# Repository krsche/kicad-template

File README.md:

# kicad-template

This repository can be used as a template for a new KiCad project.

__Features:__  
- `kicad-library` submodule included and set up for sharing custom footprints, symbols, etc.
- GitHub workflows using kibot for outputs (gerbers, pdfs, renders, etc.) and performing checks (erc, drc)
- `bootstrap.sh` script for quickly renaming your project (no need for importing this as an "OEM - KiCad Template")
- `.gitattributes` and `.gitignore` for KiCad
- Custom Design Rules according to [JLCPCB Capabilities](https://jlcpcb.com/capabilities/pcb-capabilities); modified version of https://github.com/labtroll/KiCad-DesignRules

## Getting Started
1. Create and clone a new GitHub repo for your project and select this as the template for it.
     ```bash
     gh repo create --clone --template krsche/kicad-template YOUR_REPO_NAME
     cd YOUR_REPO_NAME
     git submodule update --init --recursive
     ```
2. Run the `bootstrap.sh` script to change the name of the project files and references to your projects name. 
     Either specify the name by providing it as the first argument, or specify nothing and it will use the parent folder (repo) name.
     ```bash
     ./bootstrap.sh <OPTIONAL__PROJECT_NAME>
     ```
3. Change the `README.md`
4. Update the `LICENSE`
5. Commit the changes after running the `bootstrap.sh` script
     ```bash
     git add --all
     git commit -m "feat: bootstrap"
     git push
     ```

## Releasing
1. Observe the GH Actions already run on the commit you want to release.
     Everything looks good? --> Continue
2. Tag the commit in the format `v1.0.0` and push the tag
3. Observe the new GH Action that runs. 
     It will re-run the KiBot actions and create __a new GH Release__ with the outputs from KiBot.

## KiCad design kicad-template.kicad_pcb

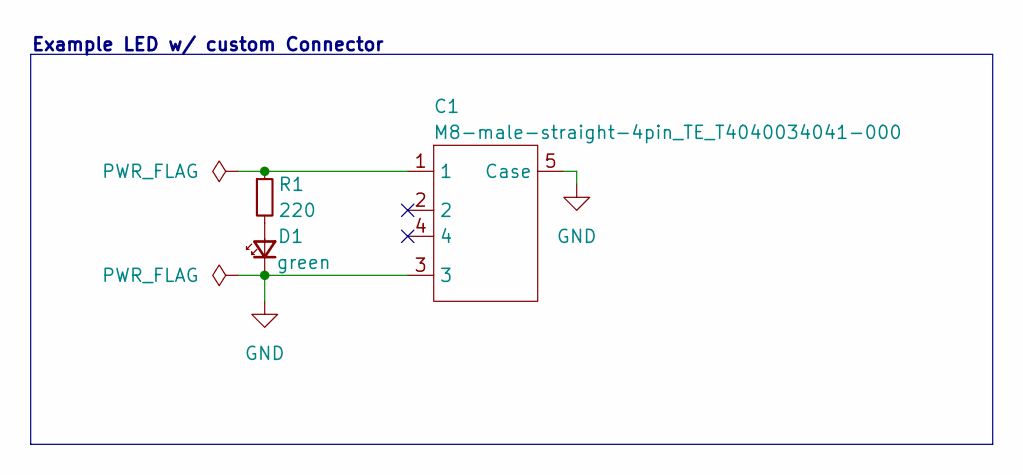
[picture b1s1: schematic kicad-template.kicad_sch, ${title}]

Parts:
C1: M8-male-straight-4pin_TE_T4040034041-000; Conn_M8_male_straight_4pin_TE_T4040034041-000; Part-Nr-Digikey A126810-ND
D1: green; LED_0603_1608Metric_Pad1.05x0.95mm_HandSolder
R1: 220; R_0603_1608Metric_Pad0.98x0.95mm_HandSolder

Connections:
GND: C1.3, C1.5 (Case), D1.1 (K)
unnamed: C1.1, R1.1
unnamed: D1.2 (A), R1.2

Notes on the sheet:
Example LED w/ custom Connector

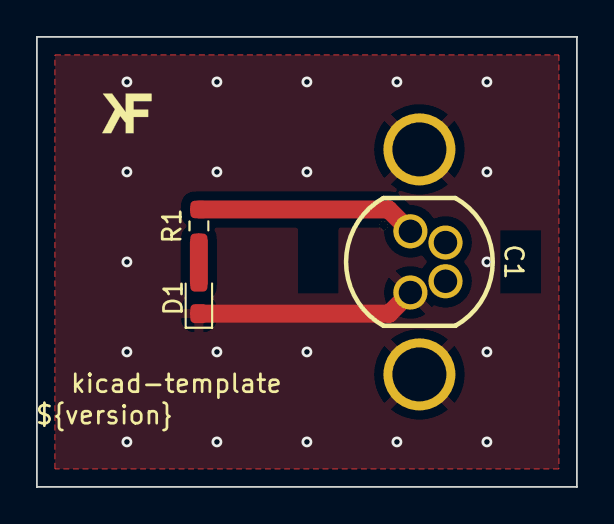
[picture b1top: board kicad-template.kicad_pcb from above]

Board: 4 copper layers, 30.0 x 25.0 mm, 3 parts (0 on the bottom side), 3 nets.

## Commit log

2022-04-21 Initial Commit
    based on trackdocs/can-socketstrip 79080c2d84e71ce2d29c4d46e88375d25e14144a
    with some modifications:
    - added bootstrap.sh
    - removed pcb and sch contents and renamed kicad_* files
    - moved kicad-library to krsche
    - updated sym-lib-table and fp-lib-table to krsche (from trackdocs)
2022-04-21 feat: Add LICENSE; updtd README, lib, actions
    - actions: no need for complicated submodule checkout anymore -
    kicad-library now public
2022-04-21 feat: moved .kibot to kicad-library submodule
2022-04-21 feat: renamed sym,fp libs & added example sch, pcb
2022-04-21 feat (bootstrap): show changes first, add excludes
2022-04-21 docs: update Release instructions (pre-release)
2022-04-21 docs: need this branch for a pr
2022-04-21 feat: rm pre-release tag, make full rel right away
2022-04-21 fix: renaming files before replacing doesn't work
2022-04-21 fix: missing submodule init & update
2022-04-21 docs: updated Getting Started steps
2024-09-05 fix: sed in bootstrap.sh not working as expected on macos
2024-11-01 feat: updated gh workflow, kicad v6 -> v8, DRUs, kicad-library
2024-11-01 feat: switched to 4-Layer PCB; updated DRU SMD Pad to Pad clearance
2024-11-03 ci: added step to init private submodules as kicad-library is now priv.
